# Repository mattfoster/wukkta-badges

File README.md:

# wukkta-badges

wukkta event badges - ready for when feroz asks.

* 2023 - Badge created with kicad 7. No special libraries/footprints.
* 2024 - Badge created with kicad 8. No special libraries/footprints. No stolen logos. Code.

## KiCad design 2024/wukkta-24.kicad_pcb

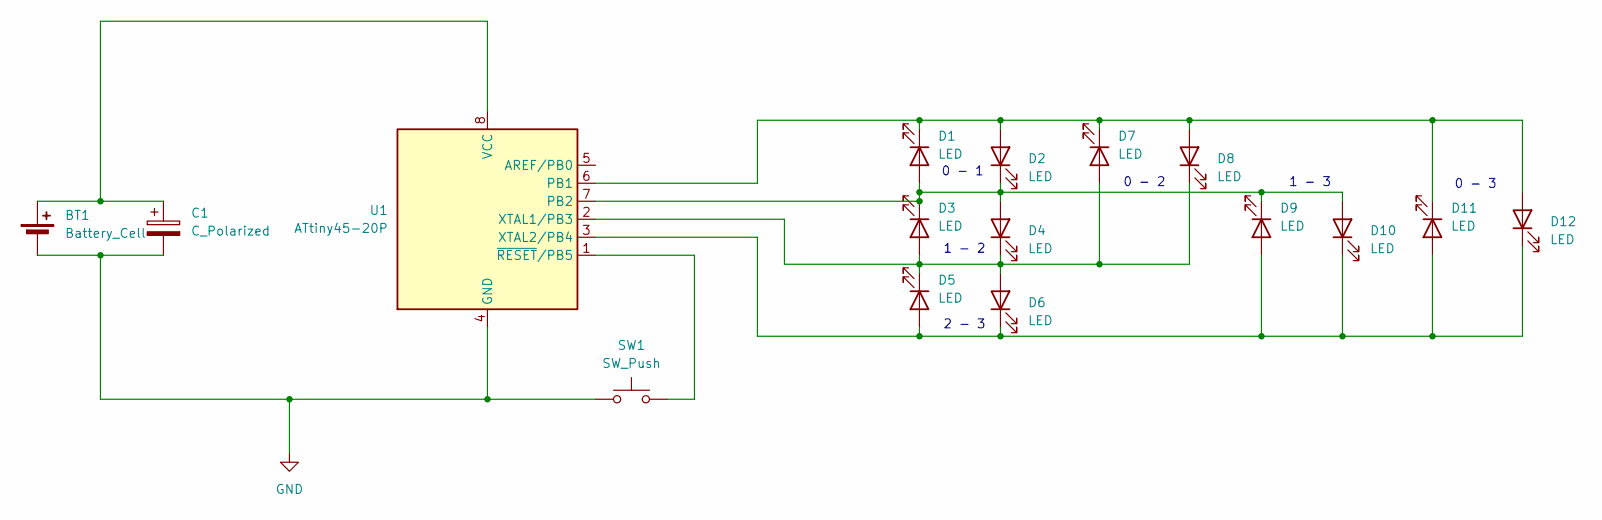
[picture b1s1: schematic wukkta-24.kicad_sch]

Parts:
BT1: Battery_Cell; BatteryHolder_Keystone_3002_1x2032
C1: C_Polarized; C_Disc_D5.0mm_W2.5mm_P2.50mm
D1, D2, D3, D4, D5, D6, D7, D8, D9, D10, D11, D12: LED; LED_D4.0mm
SW1: SW_Push; SW_PUSH_1P1T_6x3.5mm_H4.3_APEM_MJTP1243
U1: ATtiny45-20P; DIP-8_W7.62mm

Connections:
GND: BT1.2 (-), C1.2, SW1.1, U1.4 (GND)
unnamed: BT1.1 (+), C1.1, U1.8 (VCC)
unnamed: D1.2 (A), D2.1 (K), D3.1 (K), D4.2 (A), D9.1 (K), D10.2 (A), U1.7 (PB2)
unnamed: D1.1 (K), D2.2 (A), D7.1 (K), D8.2 (A), D11.1 (K), D12.2 (A), U1.6 (PB1)
unnamed: D3.2 (A), D4.1 (K), D5.1 (K), D6.2 (A), D7.2 (A), D8.1 (K), U1.2 (XTAL1/PB3)
unnamed: D5.2 (A), D6.1 (K), D9.2 (A), D10.1 (K), D11.2 (A), D12.1 (K), U1.3 (XTAL2/PB4)
unnamed: SW1.2, U1.1 (~RESET/PB5)

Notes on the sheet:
2 - 3
0 - 2
1 - 2
1 - 3
0 - 3
0 - 1

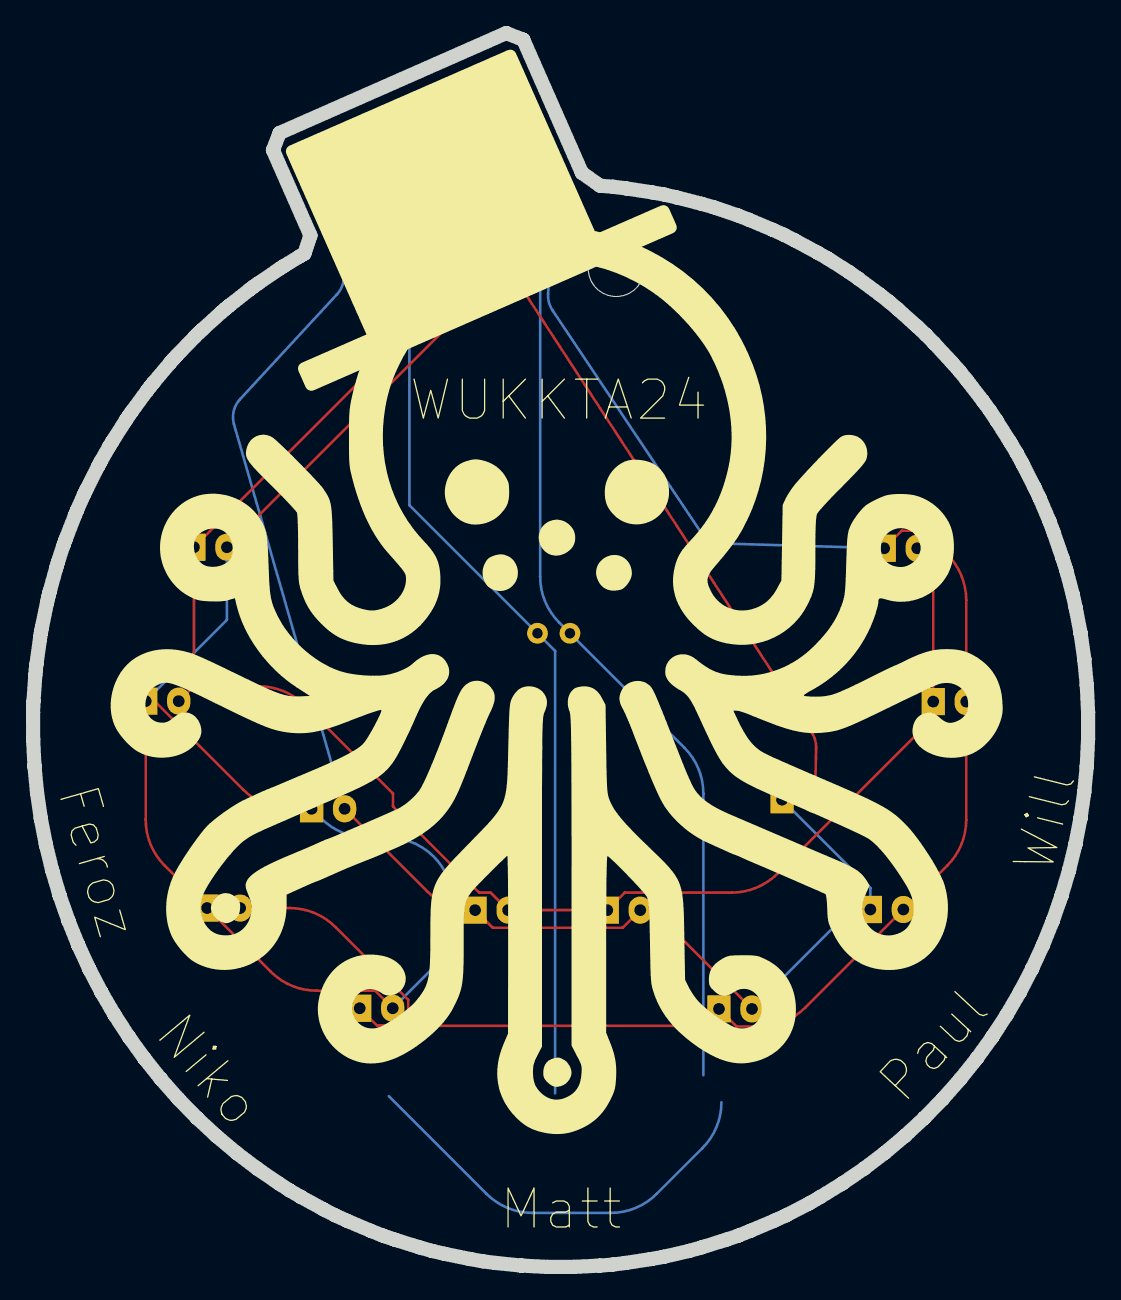
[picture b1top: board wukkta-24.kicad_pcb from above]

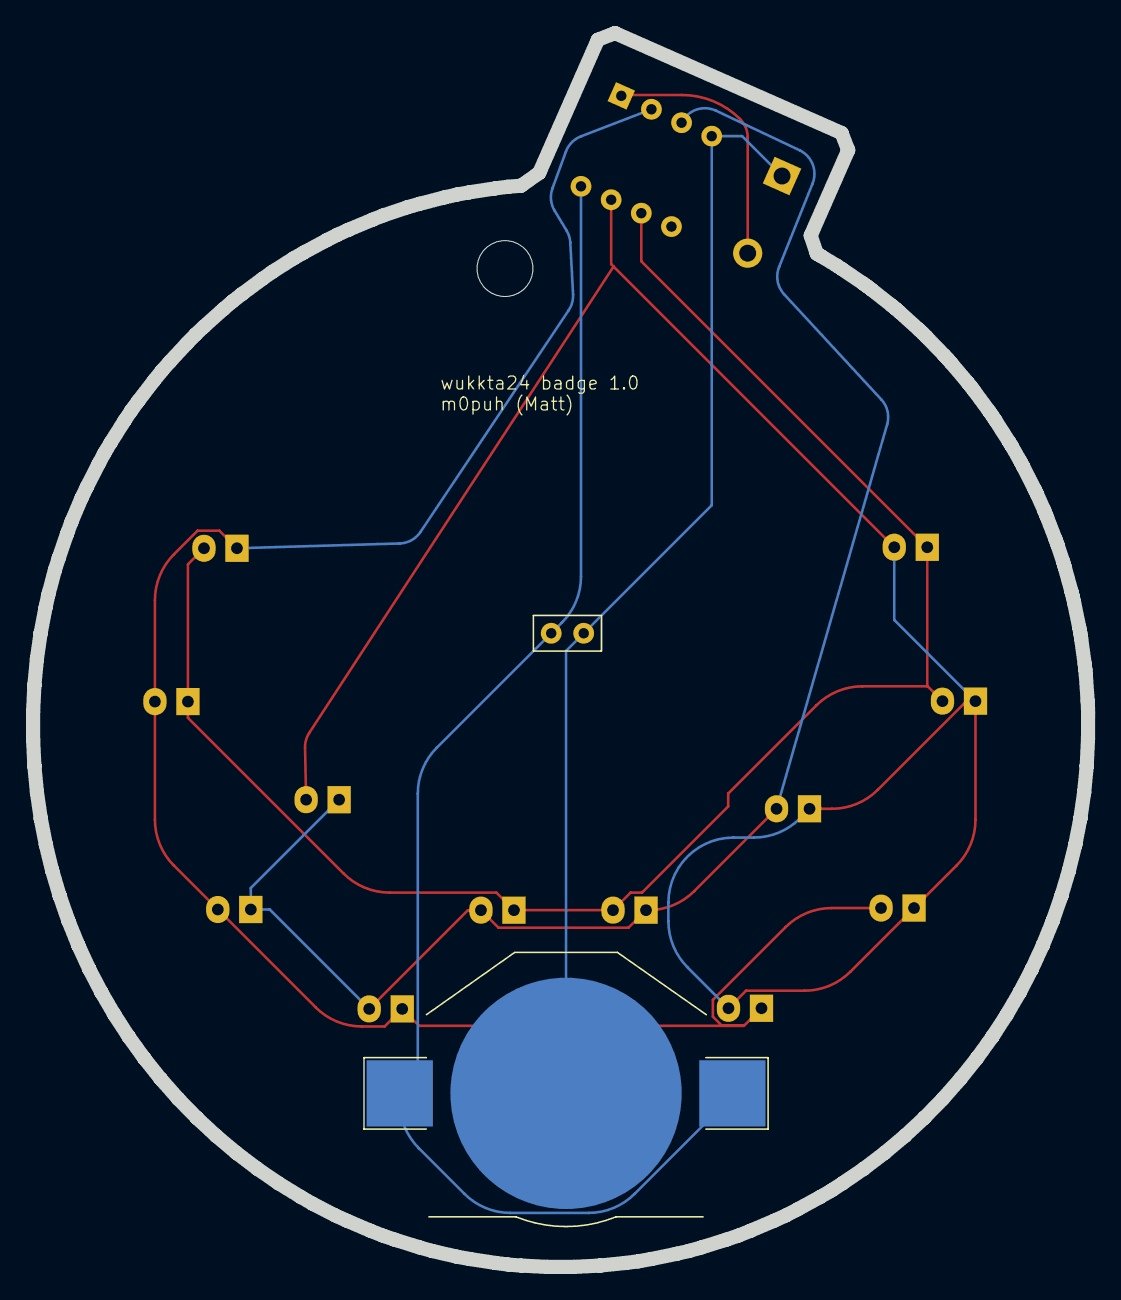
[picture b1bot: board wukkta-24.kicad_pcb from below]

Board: 2 copper layers, 81.2 x 95.0 mm, 16 parts (2 on the bottom side), 7 nets.

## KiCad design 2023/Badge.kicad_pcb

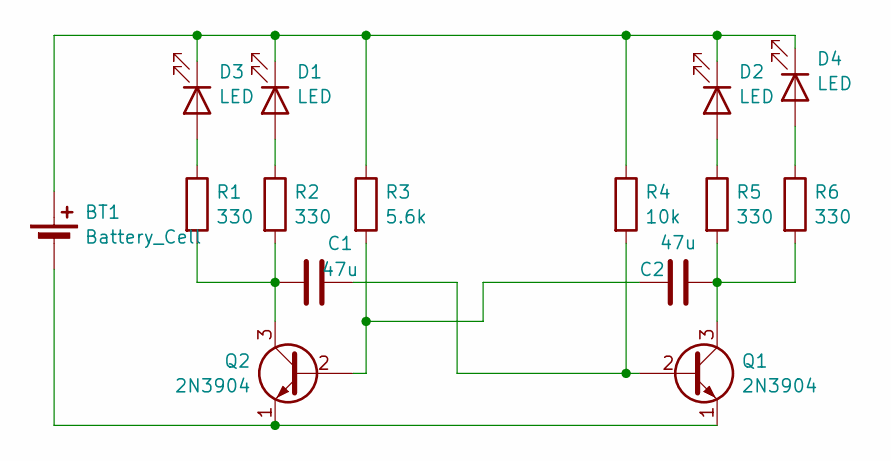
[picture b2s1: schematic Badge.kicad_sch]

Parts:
BT1: Battery_Cell; BatteryHolder_Keystone_3002_1x2032
C1, C2: 47u; CP_Radial_D5.0mm_P2.50mm
D1, D2, D3, D4: LED; LED_D3.0mm
Q1, Q2: 2N3904; TO-92_Inline
R1, R2, R5, R6: 330; R_Axial_DIN0204_L3.6mm_D1.6mm_P7.62mm_Horizontal
R3: 5.6k; R_Axial_DIN0204_L3.6mm_D1.6mm_P7.62mm_Horizontal
R4: 10k; R_Axial_DIN0204_L3.6mm_D1.6mm_P7.62mm_Horizontal

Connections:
unnamed: BT1.1 (+), D1.1 (K), D2.1 (K), D3.1 (K), D4.1 (K), R3.1, R4.1
unnamed: BT1.2 (-), Q1.1 (E), Q2.1 (E)
unnamed: D1.2 (A), R2.1
unnamed: D2.2 (A), R5.1
unnamed: D3.2 (A), R1.1
unnamed: D4.2 (A), R6.1
unnamed: C1.2, Q1.2 (B), R4.2
unnamed: C2.2, Q1.3 (C), R5.2, R6.2
unnamed: C2.1, Q2.2 (B), R3.2
unnamed: C1.1, Q2.3 (C), R1.2, R2.2

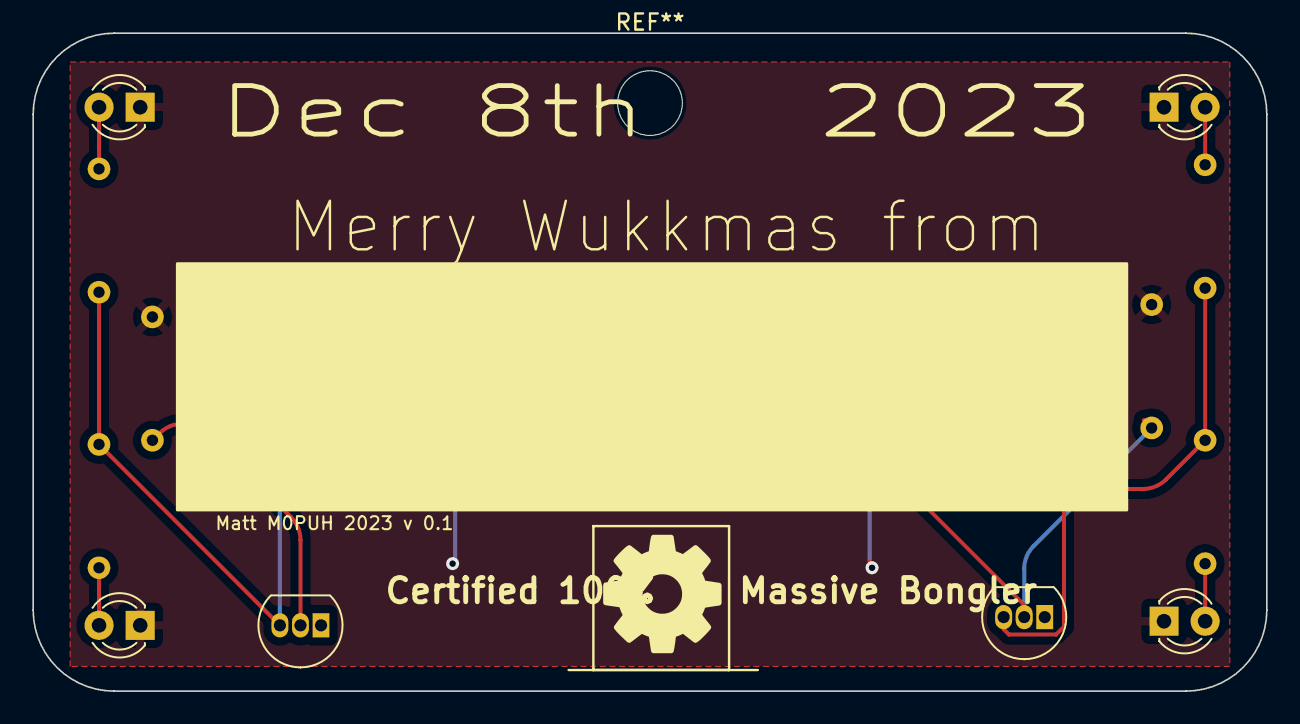
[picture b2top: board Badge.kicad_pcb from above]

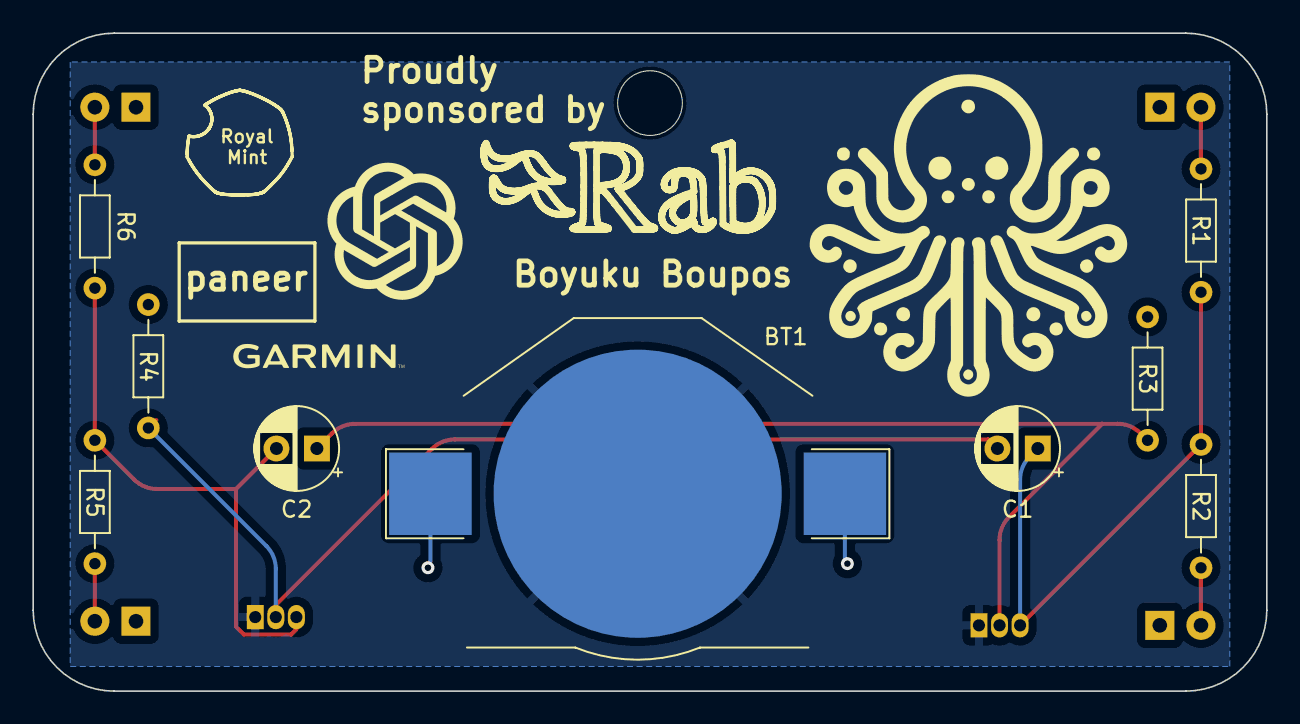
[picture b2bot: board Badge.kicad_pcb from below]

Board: 2 copper layers, 76.2 x 40.6 mm, 15 parts (9 on the bottom side), 10 nets.

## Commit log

2023-11-03 Add 2023 badge as created
    TODO:
    * move R6 label.
2023-11-03 Remove .DS_Store
2023-11-28 Add instructions
2024-11-30 Initial commit of 2024 badge
